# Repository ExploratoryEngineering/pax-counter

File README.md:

# PAX Counter

This device scans for visible bluetooth and wifi devices and then transmits the device count over NBIoT to a backend server.

Tested on ESP-WROOM-32D

## Wiring (ESP):
* VCC   3.3V
* EN    to VCC via 10k pull-up
* IO0   to GND via boot switch (enable programming mode by grounding IO0 before power-on)
* GND
* IO16    to EE-NBIoT-01 RXD
* IO17    to EE-NBIoT-01 TXD
* RXD0    a) to FTDI TX and b) to GND via 10k pull-down
* TXD0    to FTDI RX

1) Use common ground for ESP-WROOM-32D, EE-NBIoT-01 and FTDI.
2) Leave FTDI VCC pin unconnected

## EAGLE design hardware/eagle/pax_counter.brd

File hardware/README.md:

# mikroBUS PAX Counter

(Work in progress)

## BoM
* ESP-WROOM-32D
* PTS645 SMT switch
* 2 x 0402 10k resistor
* 1 x 6 pin 2.54mm pin header
* 2 x 8 pin 2.54mm pin header

[mikroBUS specification](https://download.mikroe.com/documents/standards/mikrobus/mikrobus-standard-specification-v200.pdf)

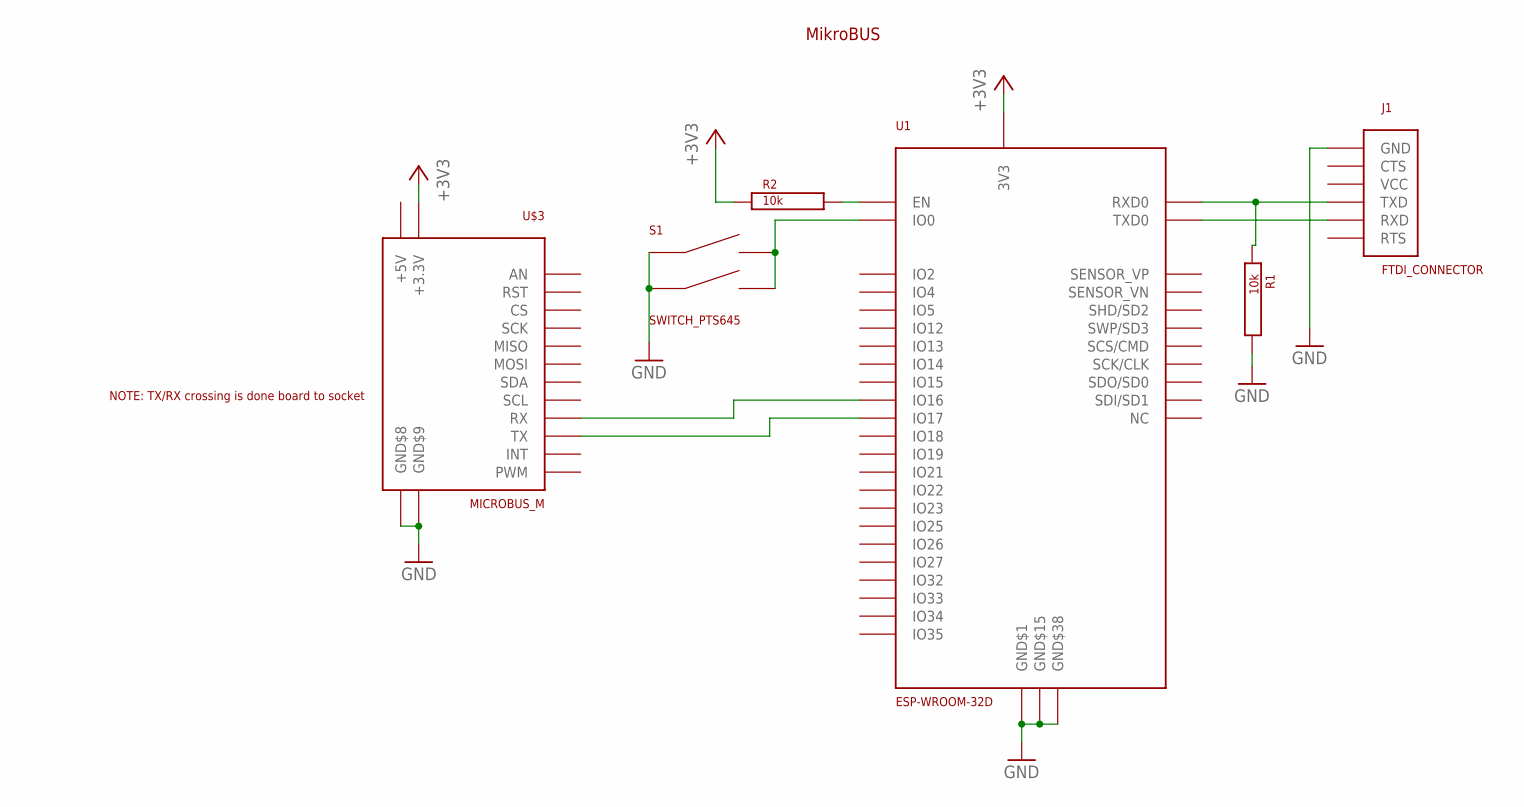
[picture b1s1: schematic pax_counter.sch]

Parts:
J1: FTDI_CONNECTOR
R1, R2: 10k; RES_0402
S1: SWITCH_PTS645; SWITCH_PTS645_EE_NBIOT_01
U1: ESP-WROOM-32D; ESP_WROOM_32D
U$1: MIKROBUS_LOGO
U$3: MICROBUS_M; MIKROBUS_M

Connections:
+3V3: R2.P$1, U1.2 (3V3), U$3.+3.3V
GND: J1.GND, R1.P$2, S1.A1, S1.A2, U1.1 (GND$1), U1.15 (GND$15), U1.38 (GND$38), U1.GND$39 (GND$38), U1.GND$40 (GND$38), U1.GND$41 (GND$38), U1.GND$42 (GND$38), U1.GND$43 (GND$38), U1.GND$44 (GND$38), U1.GND$45 (GND$38), U1.GND$46 (GND$38), U1.GND$47 (GND$38), U$3.GND$8, U$3.GND$9
unnamed: U1.27 (IO16), U$3.RX
unnamed: U1.28 (IO17), U$3.TX
unnamed: R2.P$2, U1.3 (EN)
unnamed: J1.TXD, R1.P$1, U1.34 (RXD0)
unnamed: J1.RXD, U1.35 (TXD0)
unnamed: S1.B1, S1.B2, U1.25 (IO0)

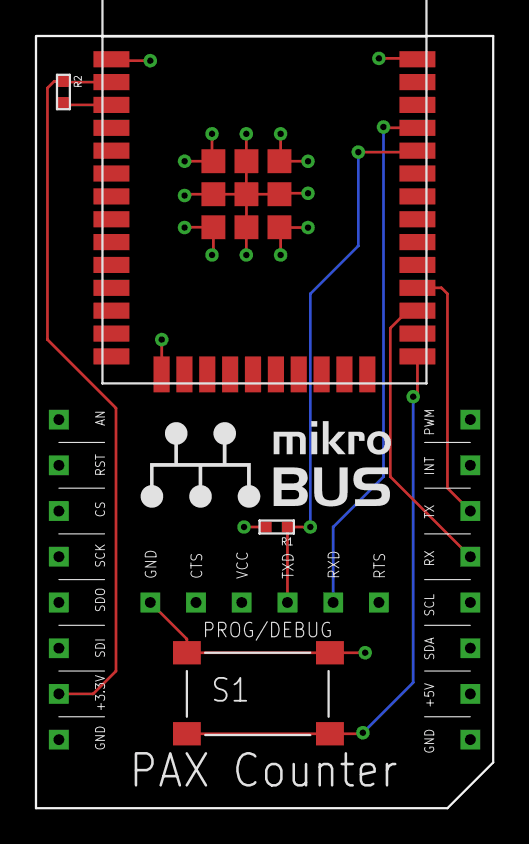
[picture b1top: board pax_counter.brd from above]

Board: 2 copper layers, 25.4 x 42.9 mm, 7 parts (0 on the bottom side), 8 nets.

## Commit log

2020-03-27 Added BT scanner code
2020-03-29 Added NBIoT library. Verified NBIoT tx
2020-03-29 Added missing header file
2020-03-29 Added wiring description
2020-03-29 Moved wiring desc to readme
2020-03-29 Added wifi scanner
2020-03-29 Added device image
2020-03-30 Added mikroBUS HW design
2020-03-30 Added Eagle snapshot of board
2020-03-31 Added missing function prototypes
2020-03-31 Added address pool with decay parameter
